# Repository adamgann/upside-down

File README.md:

# upside-down
Halloween 2019: The wall of lights from Stranger Things

---
In this costume an Arduino Uno, several shift registers (74HC595), and a handful of LEDs were used to create the wall from the first season of Stranger Things. The result can be seen [in this video](https://www.youtube.com/watch?v=mKRO_VgZO74) and the build process is discussed in [this blog post](http://adamgannon.com/2019/11/03/an-arduino-powered-stranger-things-costume/).

All design files are available to use (see terms in LICENSE). A warning this was hacked together fairly quickly, so don't expect a graceful board layout or bug-free software. Please cite this repository or my blog.

---
## Files

### arduino/
Contains Arudino sketches. Partly based on examples from [Janis Rove](https://github.com/janisrove/Arduino-74HC595-shift-registers) and the folks at [Adafruit](https://learn.adafruit.com/adafruit-arduino-lesson-4-eight-leds/brightness-control).

The sketch `check_leds.ino` cycles through each letter of the alphabet to verify wiring is correct.

The sketch `main.ino` runs through the light sequence.

### eagle/
Contains schematic and design files for the PCB. The project name is `shift_register_board`. Huge thanks to the [Sparkfun Eagle library](https://github.com/sparkfun/SparkFun-Eagle-Libraries) for footprints.

### graphics/
Files for the silkscreen logo added to the board. I followed the Eagle BMP import process discussed [in this tutorial](https://learn.sparkfun.com/tutorials/importing-custom-images-into-eagle/method-3-import-bmp).

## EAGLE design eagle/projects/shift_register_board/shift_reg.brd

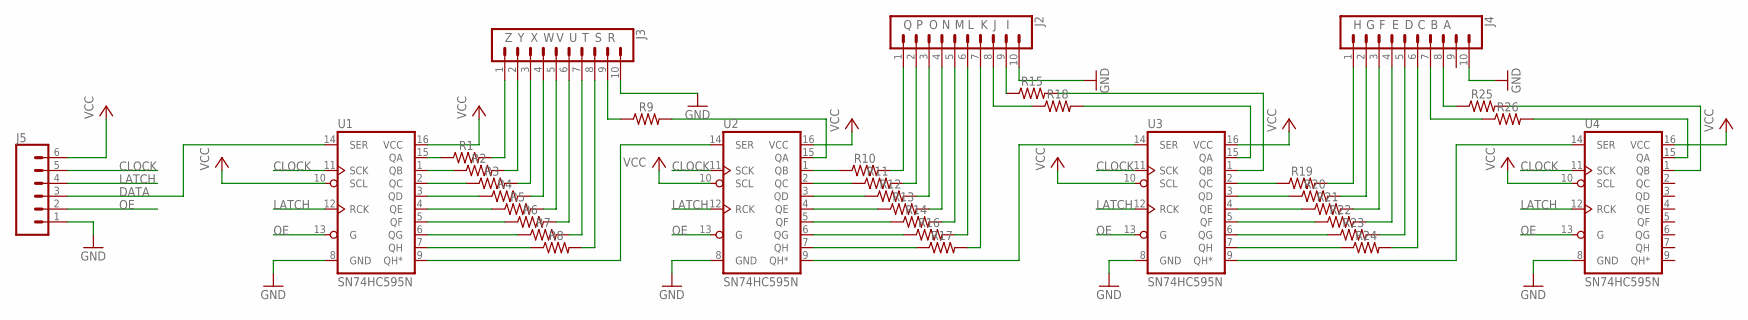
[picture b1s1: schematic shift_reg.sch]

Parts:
J2, J3, J4: CONN_10"; 1X10
J5: CONN_06LOCK; 1X06_LOCK
R1, R2, R3, R4, R5, R6, R7, R8, R9, R10, R11, R12, R13, R14, R15, R16, R17, R18, R19, R20, R21, R22, R23, R24, R25, R26: AXIAL-0.3
U1, U2, U3, U4: SN74HC595N; DIP16

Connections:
A: J4.8, R25.P$1 (1)
B: J4.7, R26.P$1 (1)
C: J4.6, R24.P$2 (2)
CLOCK: J5.5, U1.11 (SCK), U2.11 (SCK), U3.11 (SCK), U4.11 (SCK)
D: J4.5, R23.P$2 (2)
DATA: J5.3, U1.14 (SER)
E: J4.4, R22.P$2 (2)
F: J4.3, R21.P$2 (2)
G: J4.2, R20.P$2 (2)
GND: J2.10, J3.10, J4.10, J5.1, U1.8 (GND), U2.8 (GND), U3.8 (GND), U4.8 (GND)
H: J4.1, R19.P$2 (2)
I: J2.9, R15.P$1 (1)
J: J2.8, R18.P$1 (1)
K: J2.7, R17.P$2 (2)
L: J2.6, R16.P$2 (2)
LATCH: J5.4, U1.12 (RCK), U2.12 (RCK), U3.12 (RCK), U4.12 (RCK)
M: J2.5, R14.P$2 (2)
N: J2.4, R13.P$2 (2)
unnamed: U1.9 (QH*), U2.14 (SER)
unnamed: R9.P$2 (2), U2.15 (QA)
unnamed: R14.P$1 (1), U2.5 (QF)
unnamed: R18.P$2 (2), U3.15 (QA)
unnamed: R15.P$2 (2), U3.1 (QB)
unnamed: R1.P$1 (1), U1.15 (QA)
unnamed: R2.P$1 (1), U1.1 (QB)
unnamed: R3.P$1 (1), U1.2 (QC)
unnamed: R4.P$1 (1), U1.3 (QD)
unnamed: R5.P$1 (1), U1.4 (QE)
unnamed: R6.P$1 (1), U1.5 (QF)
unnamed: R7.P$1 (1), U1.6 (QG)
unnamed: R8.P$1 (1), U1.7 (QH)
unnamed: R10.P$1 (1), U2.1 (QB)
unnamed: R11.P$1 (1), U2.2 (QC)
unnamed: R12.P$1 (1), U2.3 (QD)
unnamed: R13.P$1 (1), U2.4 (QE)
unnamed: R16.P$1 (1), U2.6 (QG)
unnamed: R17.P$1 (1), U2.7 (QH)
unnamed: R19.P$1 (1), U3.2 (QC)
unnamed: R20.P$1 (1), U3.3 (QD)
unnamed: U2.9 (QH*), U3.14 (SER)
unnamed: R21.P$1 (1), U3.4 (QE)
unnamed: R22.P$1 (1), U3.5 (QF)
unnamed: R23.P$1 (1), U3.6 (QG)
unnamed: R24.P$1 (1), U3.7 (QH)
unnamed: R26.P$2 (2), U4.15 (QA)
unnamed: R25.P$2 (2), U4.1 (QB)
unnamed: U3.9 (QH*), U4.14 (SER)
O: J2.3, R12.P$2 (2)
OE: J5.2, U1.13 (G), U2.13 (G), U3.13 (G), U4.13 (G)
P: J2.2, R11.P$2 (2)
Q: J2.1, R10.P$2 (2)
R: J3.9, R9.P$1 (1)
S: J3.8, R8.P$2 (2)
T: J3.7, R7.P$2 (2)
U: J3.6, R6.P$2 (2)
V: J3.5, R5.P$2 (2)
VCC: J5.6, U1.10 (SCL), U1.16 (VCC), U2.10 (SCL), U2.16 (VCC), U3.10 (SCL), U3.16 (VCC), U4.10 (SCL), U4.16 (VCC)
W: J3.4, R4.P$2 (2)
X: J3.3, R3.P$2 (2)
Y: J3.2, R2.P$2 (2)
Z: J3.1, R1.P$2 (2)

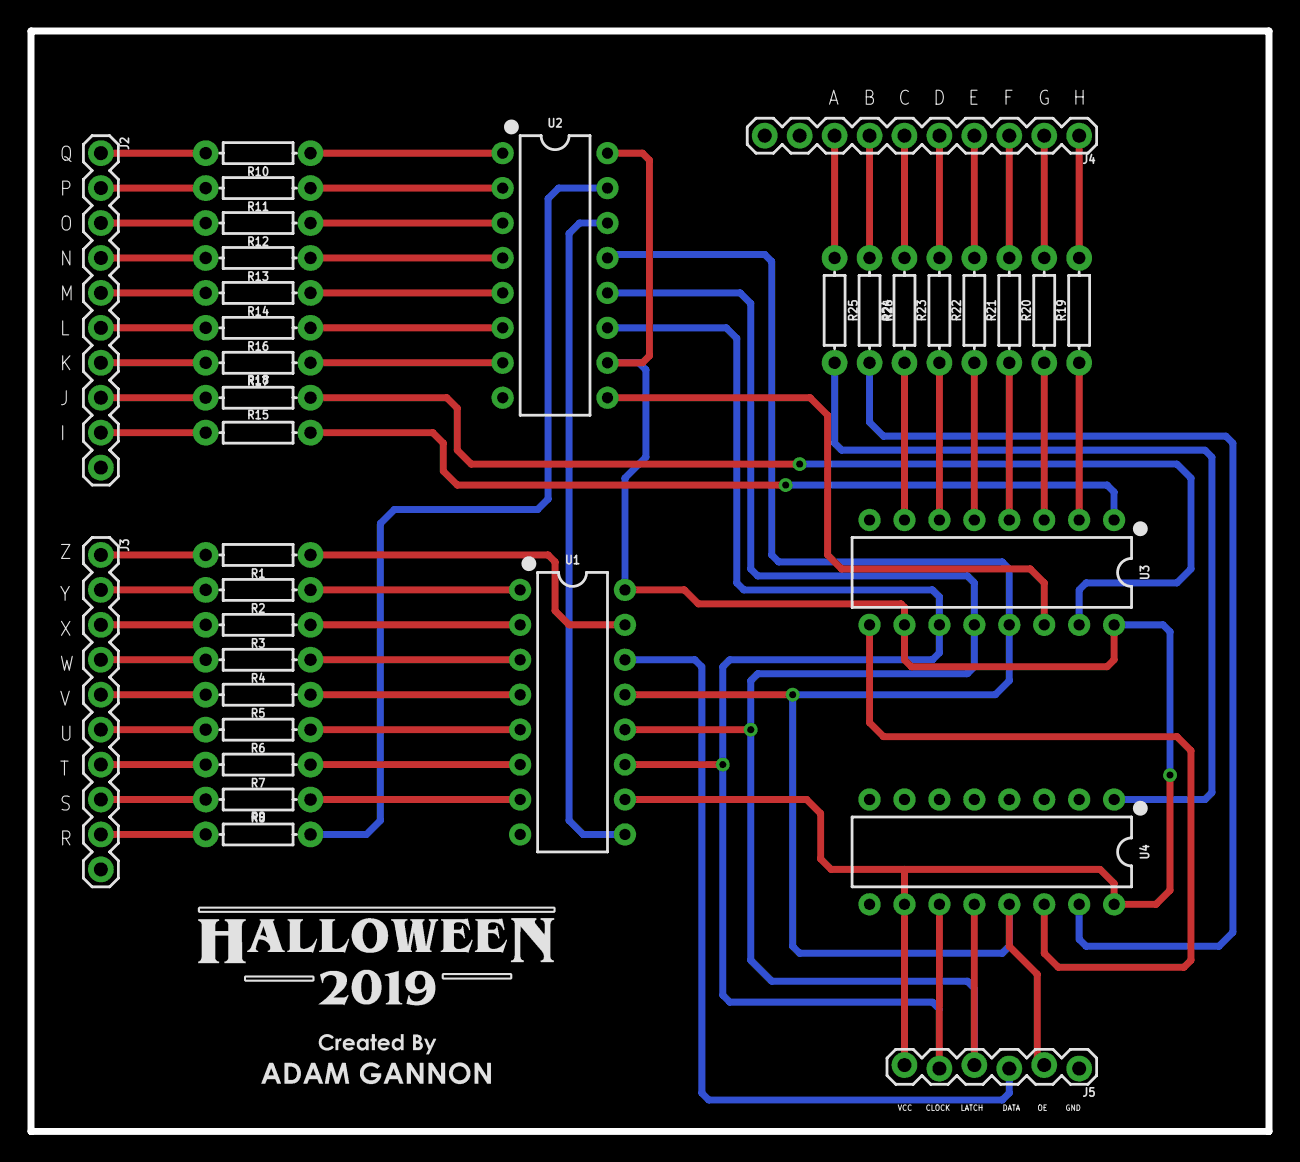
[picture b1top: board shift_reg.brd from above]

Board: 2 copper layers, 90.0 x 80.0 mm, 34 parts (0 on the bottom side), 61 nets.

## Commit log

2019-10-05 Stepping through each LED in a 3-register chain
2019-10-05 Added script to check LEDs by flashing each one in turn
2019-10-05 First draft of schematic for shift register board
2019-10-08 Started board layout
2019-10-10 Routed board.
2019-10-12 Board layout using SMD components
2019-10-12 Laid out board with through holes. Ready for pour
2019-10-13 Looks like PCB Way will work. Ready to finalize design for manufacture
2019-10-13 Added pours and silkscreen text. Ready for images
2019-10-13 Files as submitted to PCBway
2019-10-13 Got an outline of the main sequence ready
2019-10-13 Wired in button to start the sequence when pressed
2019-10-13 Minor cleanup
2019-10-13 Using an interrupt to sleep between button presses.
2019-10-26 Fixed board outline per PCB Way. Submitted updated Gerber files and design passed
2019-11-03 Updated README for public release
2019-11-03 Additional links for README
2019-11-03 Fixed README formatting
2019-11-03 Fixed README formatting for reals this time

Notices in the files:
parts and their libraries:
SparkFun-Connectors: Licensing: Creative Commons ShareAlike 4.0 International - https://creativecommons.org/licenses/by-sa/4.0
